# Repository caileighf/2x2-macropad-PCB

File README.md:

# 2x2-macropad-PCB
mechanical keyboard PCB 2x2 macro pad

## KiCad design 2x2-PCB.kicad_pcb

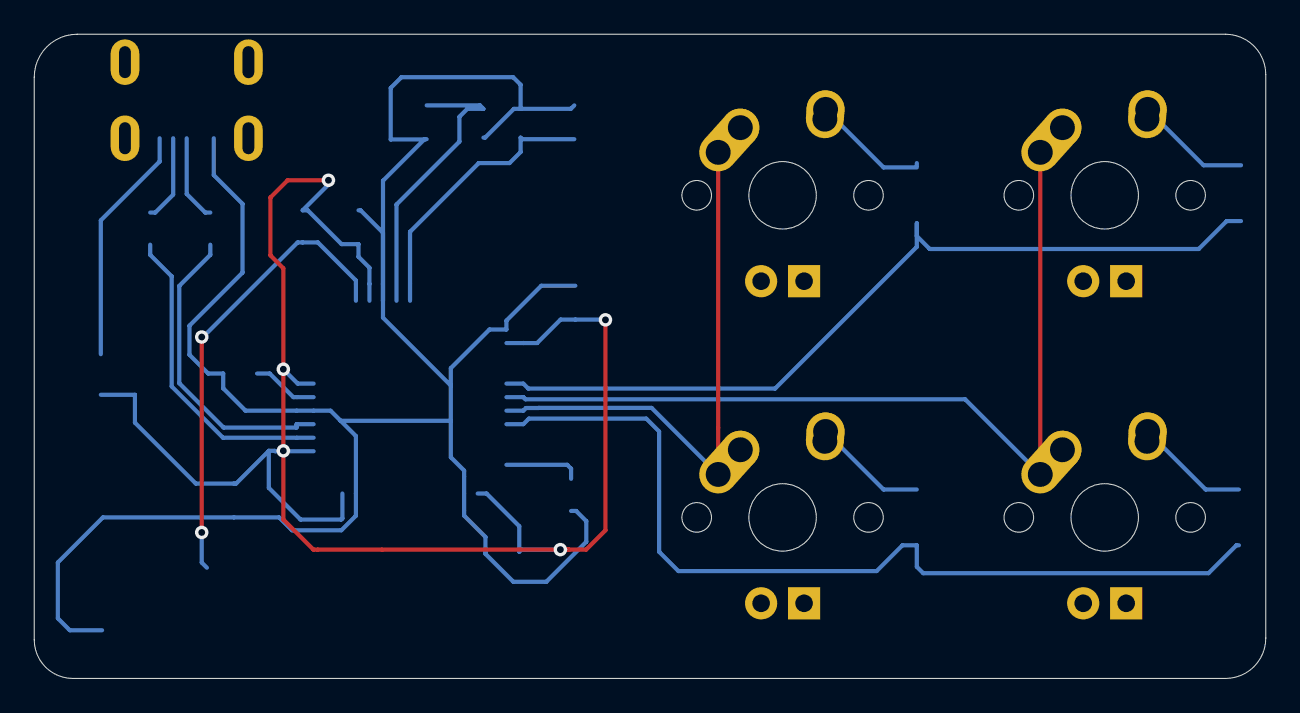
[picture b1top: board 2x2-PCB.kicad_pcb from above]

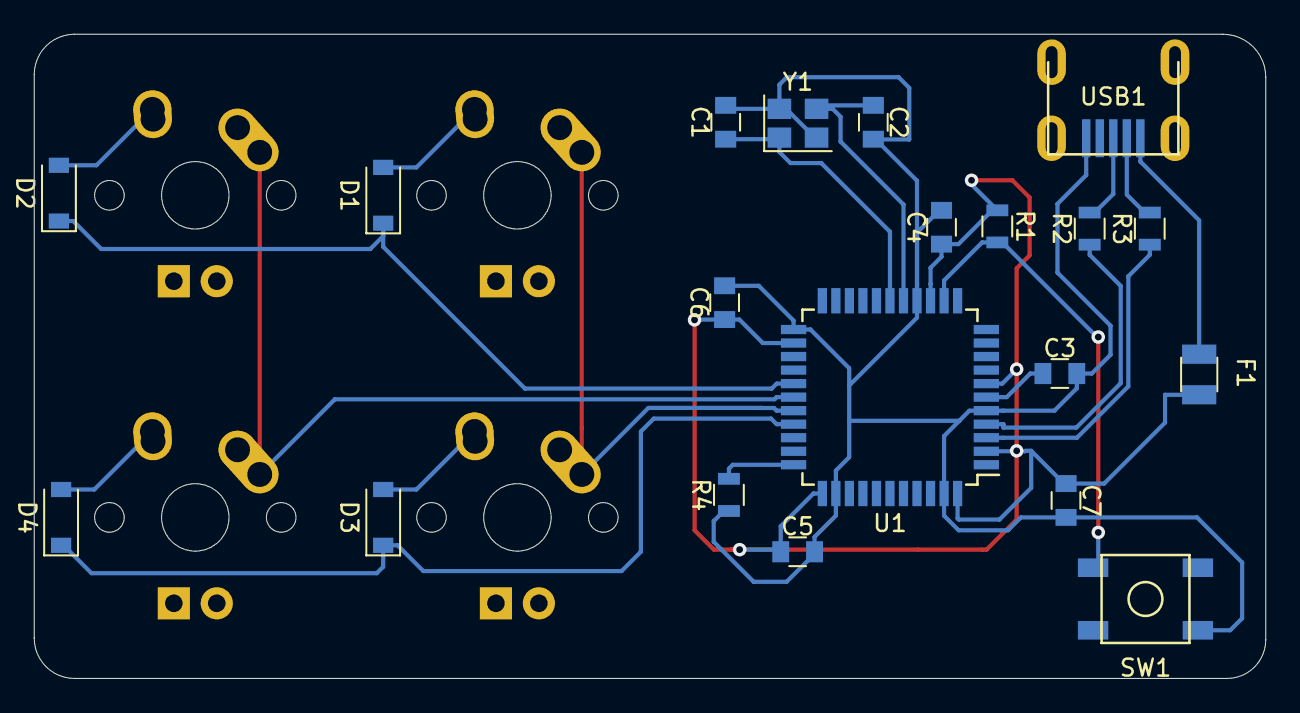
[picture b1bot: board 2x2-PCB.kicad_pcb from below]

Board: 2 copper layers, 72.8 x 38.1 mm, 24 parts (20 on the bottom side), 20 nets.

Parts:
C1, C2: 22pF; C_0805
C3: 1uF; C_0805
C4, C5, C6: 0.1uF; C_0805
C7: 10uF; C_0805
D1, D2, D3, D4: SOD-123; D_SOD-123
F1: 500mA; Fuse_SMD1206_Reflow
MX1, MX2, MX3, MX4: MX-1U
R1, R4: 10k; R_0805
R2, R3: 22; R_0805
SW1: SW_Push; SKQG-1155865
U1: ATmega32U4-AU; TQFP-44_10x10mm_Pitch0.8mm
USB1: Molex-0548190589
Y1: 16MHz; Crystal_SMD_3225-4pin_3.2x2.5mm

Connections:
+5V: C4.1, C5.1, C6.1, C7.1, F1.2, R1.1, U1.2, U1.7, U1.14, U1.24, U1.34, U1.44
COL0: MX1.1, MX3.1, U1.29
COL1: MX2.1, MX4.1, U1.28
D+: R2.2, USB1.3
D-: R3.2, USB1.4
GND: C1.2, C2.2, C3.2, C4.2, C5.2, C6.2, C7.2, R4.1, SW1.1, U1.5, U1.15, U1.23, U1.35, U1.43, USB1.1, Y1.2, Y1.4
unnamed: C1.1, U1.17, Y1.1
unnamed: C2.1, U1.16, Y1.3
unnamed: C3.1, U1.6
unnamed: D1.2, MX1.2
unnamed: D2.2, MX2.2
unnamed: D3.2, MX3.2
unnamed: D4.2, MX4.2
unnamed: R1.2, SW1.2, U1.13
unnamed: R2.1, U1.4
unnamed: R3.1, U1.3
unnamed: R4.2, U1.33
ROW0: D1.1, D2.1, U1.27
ROW1: D3.1, D4.1, U1.30
VCC: F1.1, USB1.5

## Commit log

2019-05-28 added kicad files
2019-05-28 added submodules
2019-05-28 finished schematic
2019-05-28 placed all components on board
2019-05-28 untangled design - ready for tracks
2019-05-28 re-organized - no tracks yet
2019-05-29 added tracks and traces
